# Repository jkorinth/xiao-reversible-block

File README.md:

# xiao-reversible-block

A KiCAD10 design block containing a schematic and layout for Seeed
XIAO-compatible MCU boards: Provides a reversible low-profile socket footprint
for Mill-Max or similar sockets. Fully reversible with 0R-bridges to select the
top or bottom side.

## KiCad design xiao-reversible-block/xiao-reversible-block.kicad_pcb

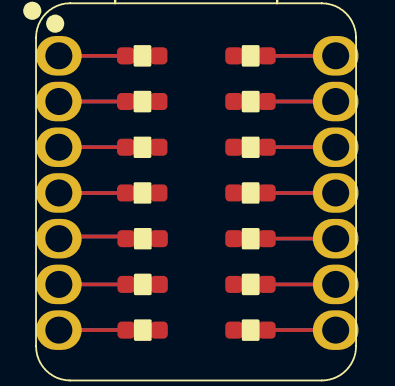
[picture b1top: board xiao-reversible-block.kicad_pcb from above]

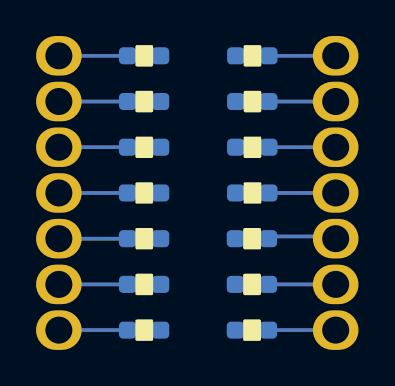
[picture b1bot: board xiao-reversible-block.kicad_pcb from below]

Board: 2 copper layers, 29 parts (14 on the bottom side), 28 nets.

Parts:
RL1, RL2, RL3, RL4, RL5, RL6, RL7, RL8, RL9, RL10, RL11, RL12, RL13, RL14: 0R; R_0603_1608Metric_Pad0.98x0.95mm_HandSolder_0R
RR1, RR2, RR3, RR4, RR5, RR6, RR7, RR8, RR9, RR10, RR11, RR12, RR13, RR14: 0R; R_0603_1608Metric_Pad0.98x0.95mm_HandSolder_0R
U1: XIAO-nRF52840-DIP; XIAO-nRF52840-LowProfileSockets-Reversible

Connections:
+3V3: RL12.2, RR3.2
+5V: RL14.2, RR1.2
/P0.03_A1_D1: RL2.1, RR13.1
/P0.04_A4_D4_SDA: RL5.1, RR10.1
/P0.05_A5_D5_SCL: RL6.1, RR9.1
/P0.28_A2_D2: RL3.1, RR12.1
/P0.29_A3_D3: RL4.1, RR11.1
/P1.11_D6_TX: RL7.1, RR8.1
/P1.12_D7_RX: RL8.2, RR7.2
/P1.13_D8_SCK: RL9.2, RR6.2
/P1.14_D9_MISO: RL10.2, RR5.2
/P1.15_D10_MOSI: RL11.2, RR4.2
/P.0.02_A0_D0: RL1.1, RR14.1
GND: RL13.2, RR2.2
unnamed: RL12.1, RR12.2, U1.12 (3V3)
unnamed: RL13.1, RR13.2, U1.13 (GND)
unnamed: RL1.2, RR1.1, U1.1 (P0.02_A0_D0)
unnamed: RL2.2, RR2.1, U1.2 (P0.03_A1_D1)
unnamed: RL5.2, RR5.1, U1.5 (P0.04_A4_D4_SDA)
unnamed: RL6.2, RR6.1, U1.6 (P0.05_A5_D5_SCL)
unnamed: RL3.2, RR3.1, U1.3 (P0.28_A2_D2)
unnamed: RL4.2, RR4.1, U1.4 (P0.29_A3_D3)
unnamed: RL7.2, RR7.1, U1.7 (P1.11_D6_TX)
unnamed: RL8.1, RR8.2, U1.8 (P1.12_D7_RX)
unnamed: RL9.1, RR9.2, U1.9 (P1.13_D8_SCK)
unnamed: RL10.1, RR10.2, U1.10 (P1.14_D9_MISO)
unnamed: RL11.1, RR11.2, U1.11 (P1.15_D10_MOSI)
unnamed: RL14.1, RR14.2, U1.14 (VBUS)

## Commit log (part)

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2026-05-09 feat: initial version of design block
2026-05-09 refactor: bugfixes, refinements
    - fix netnames: no _L/_R suffix required, same nets
    - added traces to through holes
    - fixed orientation of 0R resistors
    - ungrouped 0R resistors (too difficult to access)
2026-05-10 fix: switch h-labels to labels
2026-05-10 fix(block): update design block
2026-05-10 fix: fix bugs and improve
    - typo: SDL -> SDA
    - replaced GND net by actual ground symbol
    - fixed power flags for ERC
2026-05-13 fix(footprint): fix courtyards to allow placing in between rows
2026-06-19 fix(xiao-lp): fix footprint - header rows were space too wide by 2.54mm
